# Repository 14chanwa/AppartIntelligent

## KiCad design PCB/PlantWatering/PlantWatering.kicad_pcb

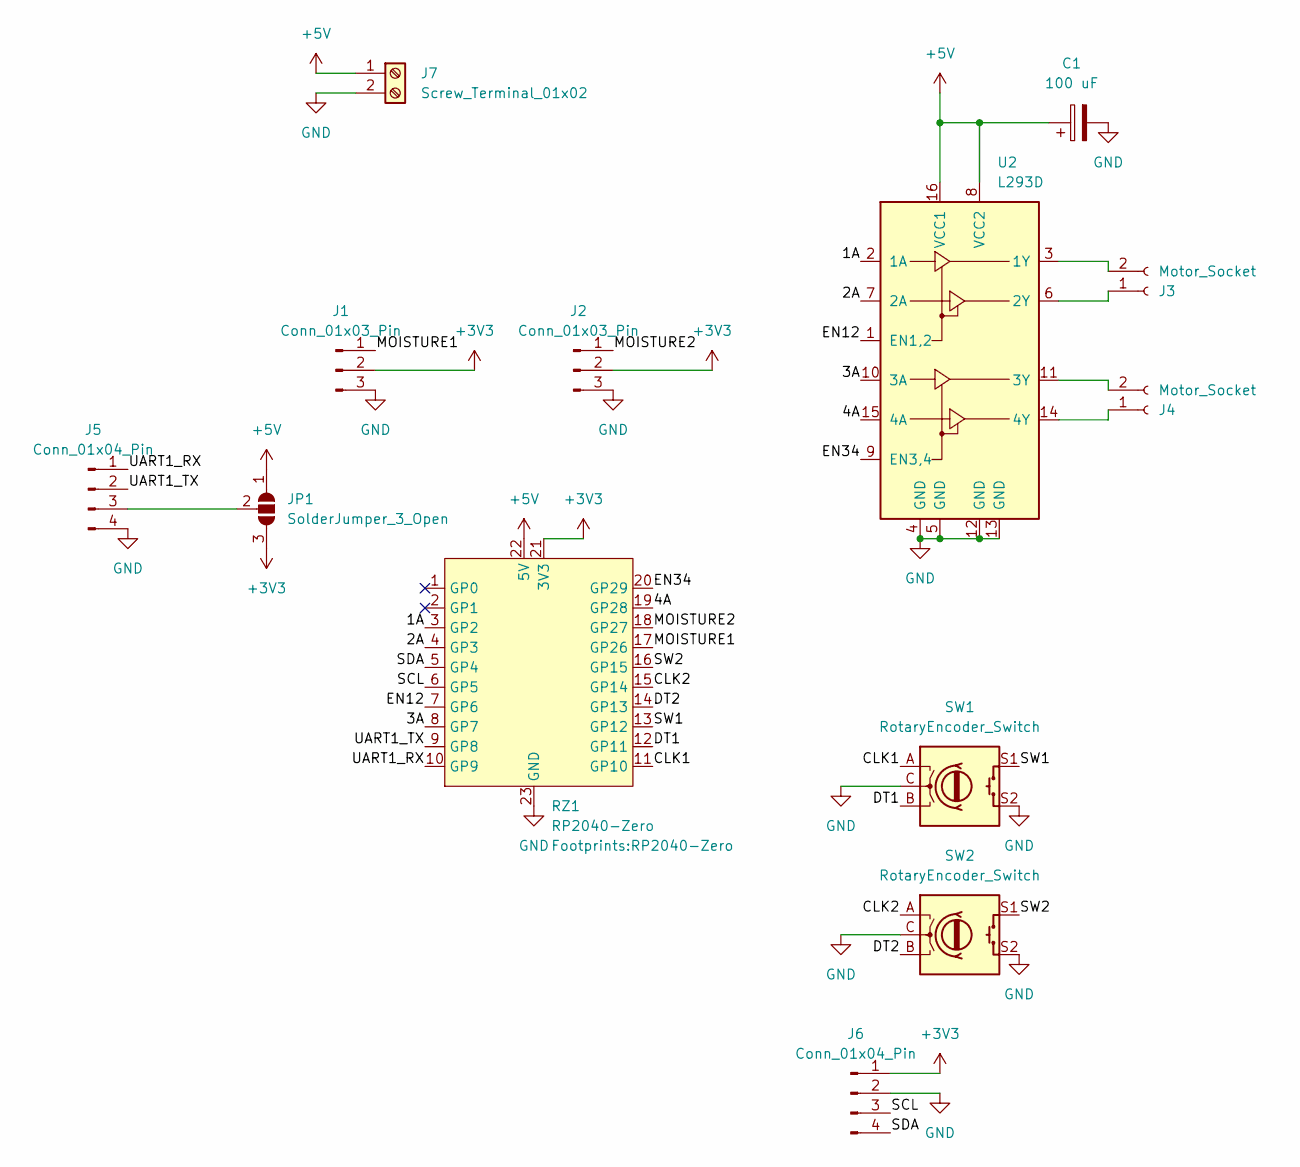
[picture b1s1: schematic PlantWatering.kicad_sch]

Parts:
C1: 100 uF; CP_Radial_D5.0mm_P2.50mm
J1, J2: Conn_01x03_Pin; PinHeader_1x03_P2.54mm_Vertical
J3, J4: Motor_Socket; PumpWatering
J5: Conn_01x04_Pin; PinHeader_1x04_P2.54mm_Vertical
J6: Conn_01x04_Pin; SSD1306
J7: Screw_Terminal_01x02; USBC-Dummy-Card
JP1: SolderJumper_3_Open; SolderJumper-3_P1.3mm_Open_RoundedPad1.0x1.5mm_NumberLabels
RZ1: RP2040-Zero
SW1, SW2: RotaryEncoder_Switch; RotaryEncoder_Alps_EC11E-Switch_Vertical_H20mm
U2: L293D; DIP-16_W7.62mm

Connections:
+3V3: J1.2, J2.2, J6.1, JP1.3 (B), RZ1.21 (3V3)
+5V: C1.1, J7.1, JP1.1 (A), RZ1.22 (5V), U2.8 (VCC2), U2.16 (VCC1)
/1A: RZ1.3 (GP2), U2.2 (1A)
/2A: RZ1.4 (GP3), U2.7 (2A)
/3A: RZ1.8 (GP7), U2.10 (3A)
/4A: RZ1.19 (GP28), U2.15 (4A)
/CLK1: RZ1.11 (GP10), SW1.A
/CLK2: RZ1.15 (GP14), SW2.A
/DT1: RZ1.12 (GP11), SW1.B
/DT2: RZ1.14 (GP13), SW2.B
/EN12: RZ1.7 (GP6), U2.1 (EN1,2)
/EN34: RZ1.20 (GP29), U2.9 (EN3,4)
/MOISTURE1: J1.1, RZ1.17 (GP26)
/MOISTURE2: J2.1, RZ1.18 (GP27)
/SCL: J6.3, RZ1.6 (GP5)
/SDA: J6.4, RZ1.5 (GP4)
/SW1: RZ1.13 (GP12), SW1.S1
/SW2: RZ1.16 (GP15), SW2.S1
/UART1_RX: J5.1, RZ1.10 (GP9)
/UART1_TX: J5.2, RZ1.9 (GP8)
GND: C1.2, J1.3, J2.3, J5.4, J6.2, J7.2, RZ1.23 (GND), SW1.C, SW1.S2, SW2.C, SW2.S2, U2.4 (GND), U2.5 (GND), U2.12 (GND), U2.13 (GND)
unnamed: J3.1, U2.6 (2Y)
unnamed: J3.2, U2.3 (1Y)
unnamed: J4.1, U2.14 (4Y)
unnamed: J4.2, U2.11 (3Y)
unnamed: J5.3, JP1.2 (C)

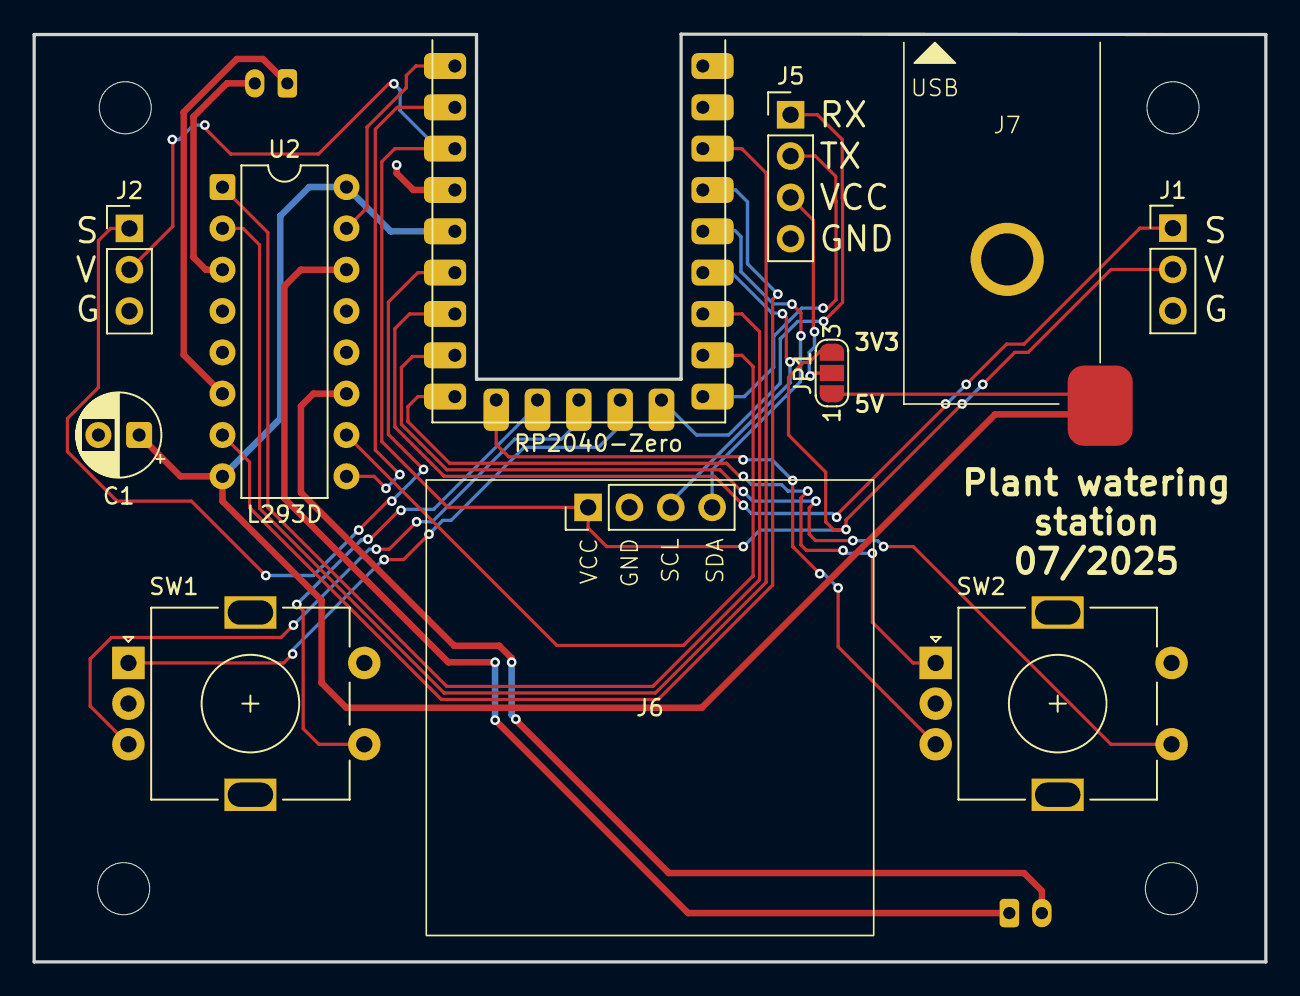
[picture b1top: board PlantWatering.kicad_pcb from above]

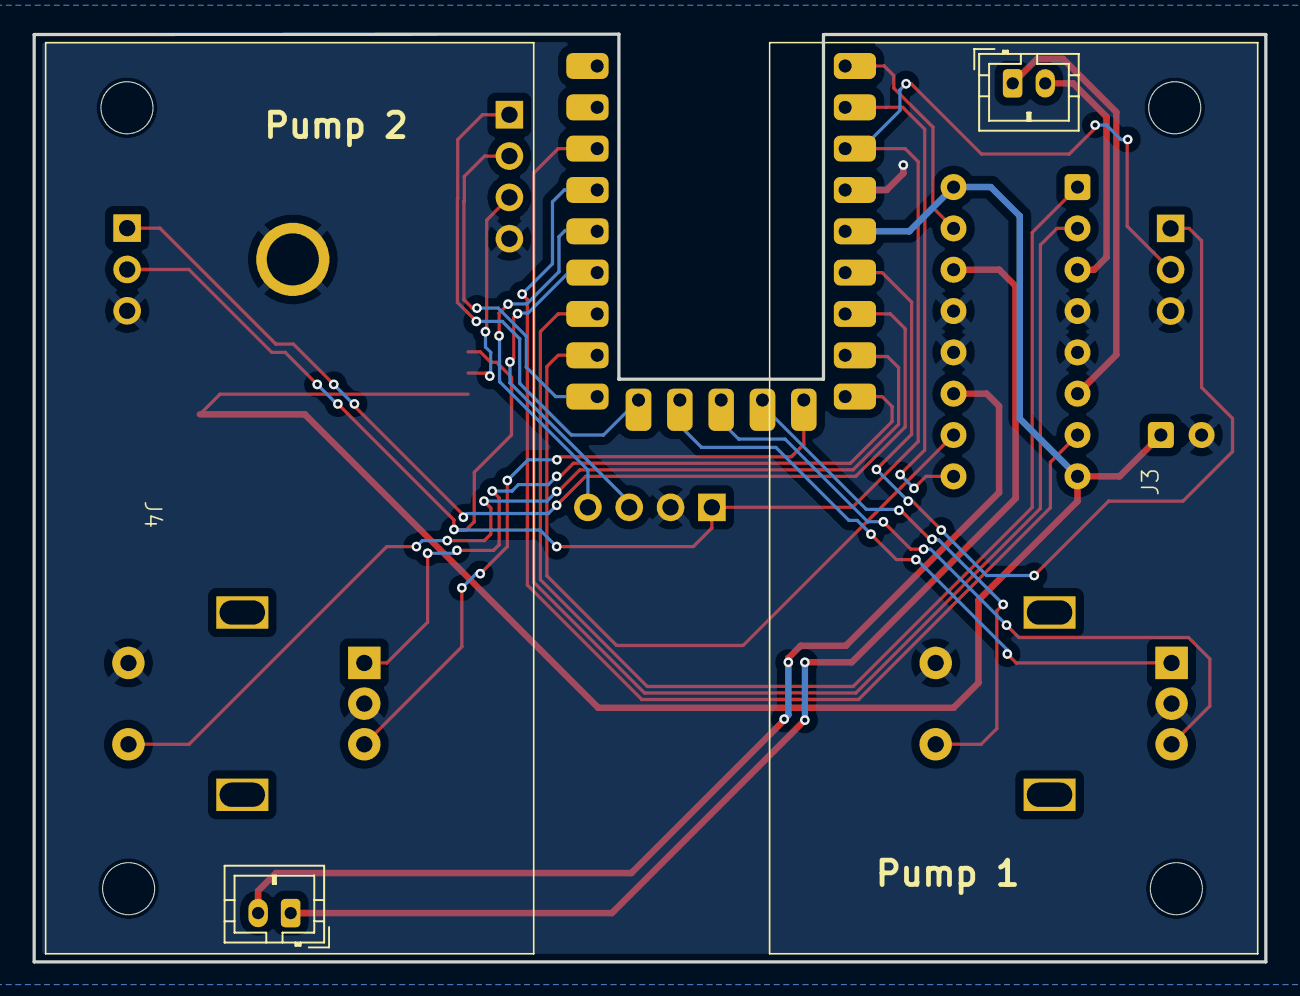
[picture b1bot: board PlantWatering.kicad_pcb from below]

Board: 2 copper layers, 75.7 x 57.0 mm, 13 parts (2 on the bottom side), 26 nets.

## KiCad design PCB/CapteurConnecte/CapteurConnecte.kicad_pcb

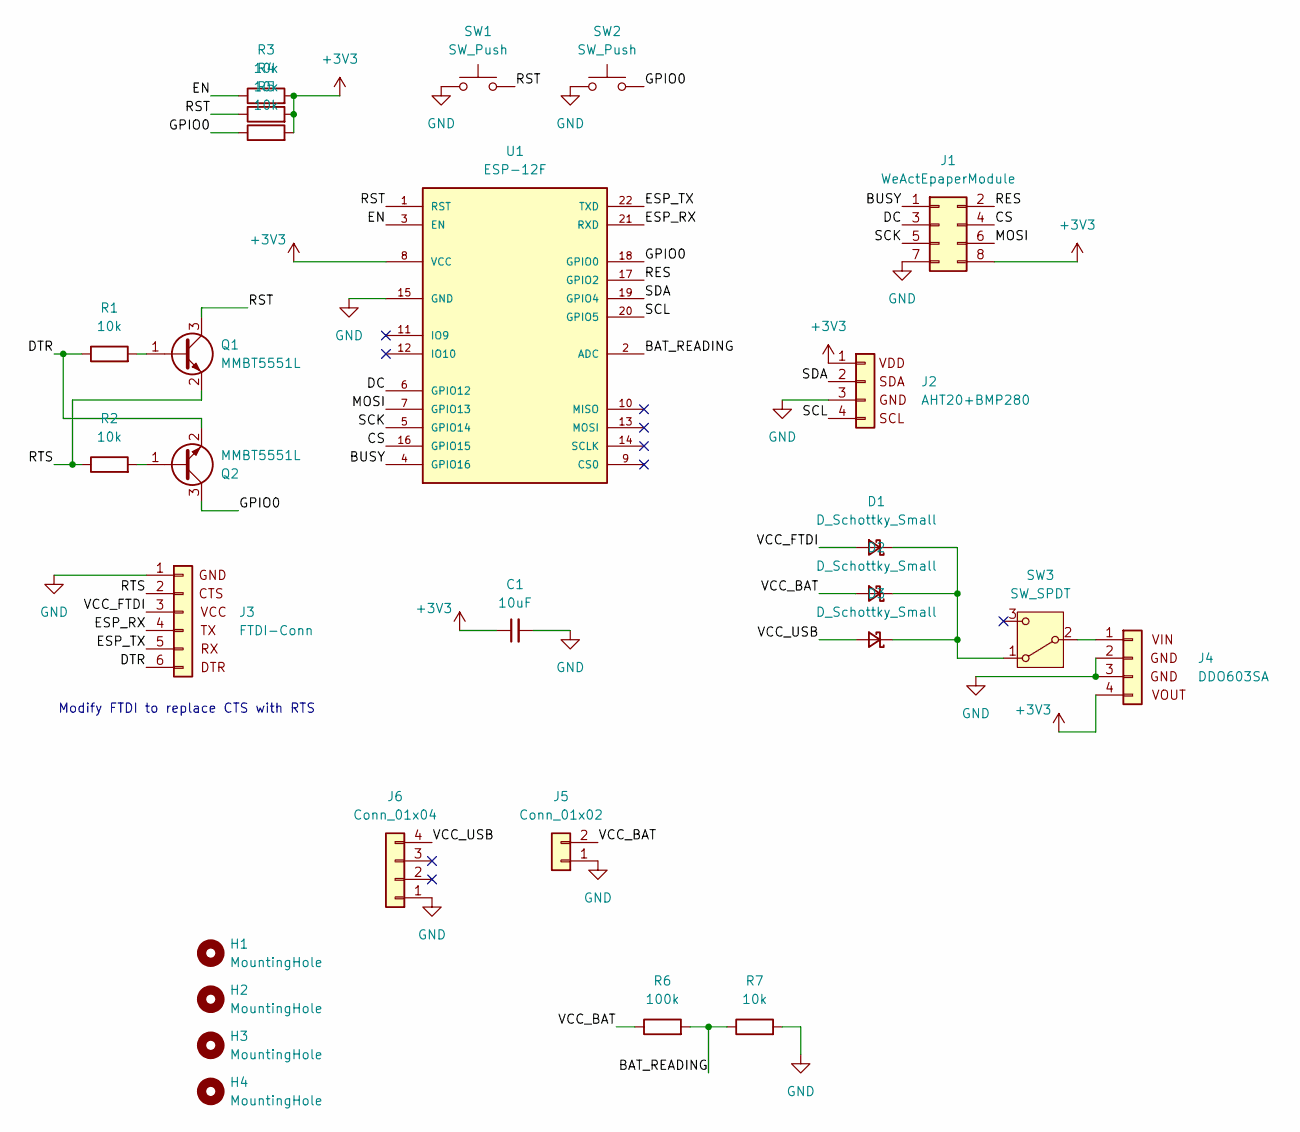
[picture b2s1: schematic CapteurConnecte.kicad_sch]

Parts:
C1: 10uF; CP_Radial_D4.0mm_P1.50mm
D1, D2, D3: D_Schottky_Small; D_SOD-323_HandSoldering
H1, H2, H3, H4: MountingHole; MountingHole_3.2mm_M3
J1: WeActEpaperModule; PinHeader_2x04_P2.54mm_Vertical
J2: AHT20+BMP280
J3: FTDI-Conn; FTDI-breakout
J4: DDO603SA; DD0603SB
J5: Conn_01x02; JST_PH_B2B-PH-K_1x02_P2.00mm_Vertical
J6: Conn_01x04; USBC-breakout
Q1, Q2: MMBT5551L; SOT-23
R1, R2, R3, R4, R5, R7: 10k; R_0805_2012Metric_Pad1.20x1.40mm_HandSolder
R6: 100k; R_0805_2012Metric_Pad1.20x1.40mm_HandSolder
SW1, SW2: SW_Push; SW_SPST_CK_RS282G05A3
SW3: SW_SPDT; SliderSwitch
U1: ESP-12F

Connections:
+3V3: C1.1, J1.8, J2.1, J4.4, R3.2, R4.2, R5.2, U1.8 (VCC)
/BAT_READING: R6.2, R7.1, U1.2 (ADC)
/BUSY: J1.1, U1.4 (GPIO16)
/CS: J1.4, U1.16 (GPIO15)
/DC: J1.3, U1.6 (GPIO12)
/DTR: J3.6, Q2.2 (E), R1.1
/EN: R3.1, U1.3 (EN)
/ESP_RX: J3.4, U1.21 (RXD)
/ESP_TX: J3.5, U1.22 (TXD)
/GPIO0: Q2.3 (C), R5.1, SW2.2, U1.18 (GPIO0)
/MOSI: J1.6, U1.7 (GPIO13)
/RES: J1.2, U1.17 (GPIO2)
/RST: Q1.3 (C), R4.1, SW1.2, U1.1 (RST)
/RTS: J3.2, Q1.2 (E), R2.1
/SCK: J1.5, U1.5 (GPIO14)
/SCL: J2.4, U1.20 (GPIO5)
/SDA: J2.2, U1.19 (GPIO4)
/VCC_BAT: D2.2 (A), J5.2, R6.1
/VCC_FTDI: D1.2 (A), J3.3
/VCC_USB: D3.2 (A), J6.4
GND: C1.2, J1.7, J2.3, J3.1, J4.2, J4.3, J5.1, J6.1, R7.2, SW1.1, SW2.1, U1.15 (GND)
unnamed: D1.1 (K), D2.1 (K), D3.1 (K), SW3.1 (A)
unnamed: J4.1, SW3.2 (B)
unnamed: Q1.1 (B), R1.2
unnamed: Q2.1 (B), R2.2

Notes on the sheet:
Modify FTDI to replace CTS with RTS

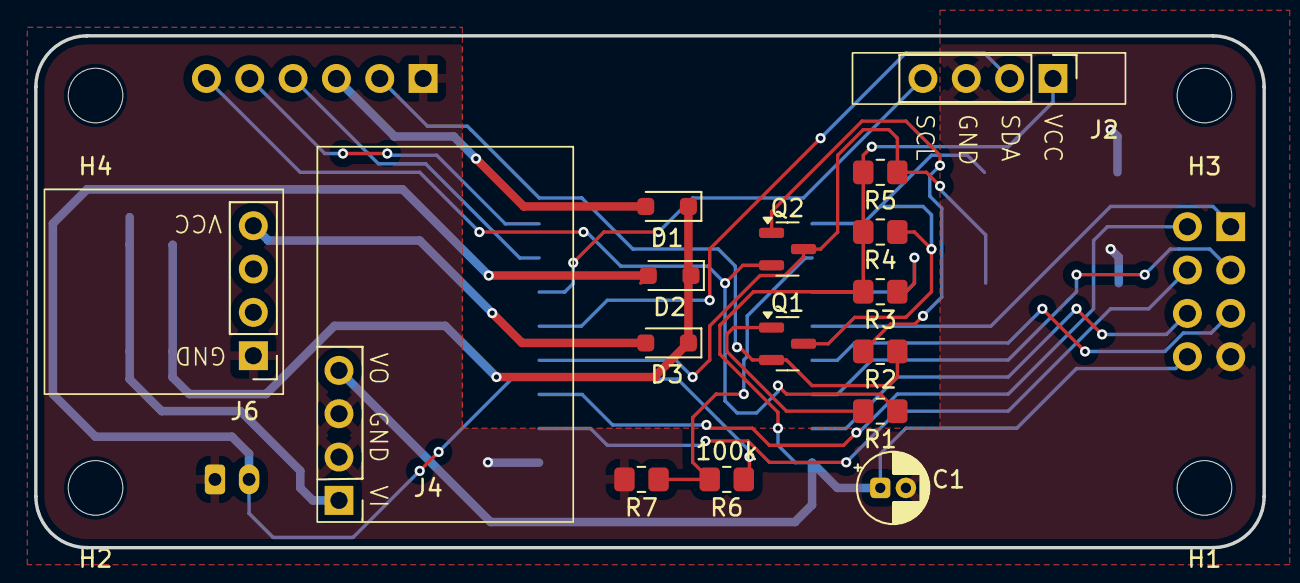
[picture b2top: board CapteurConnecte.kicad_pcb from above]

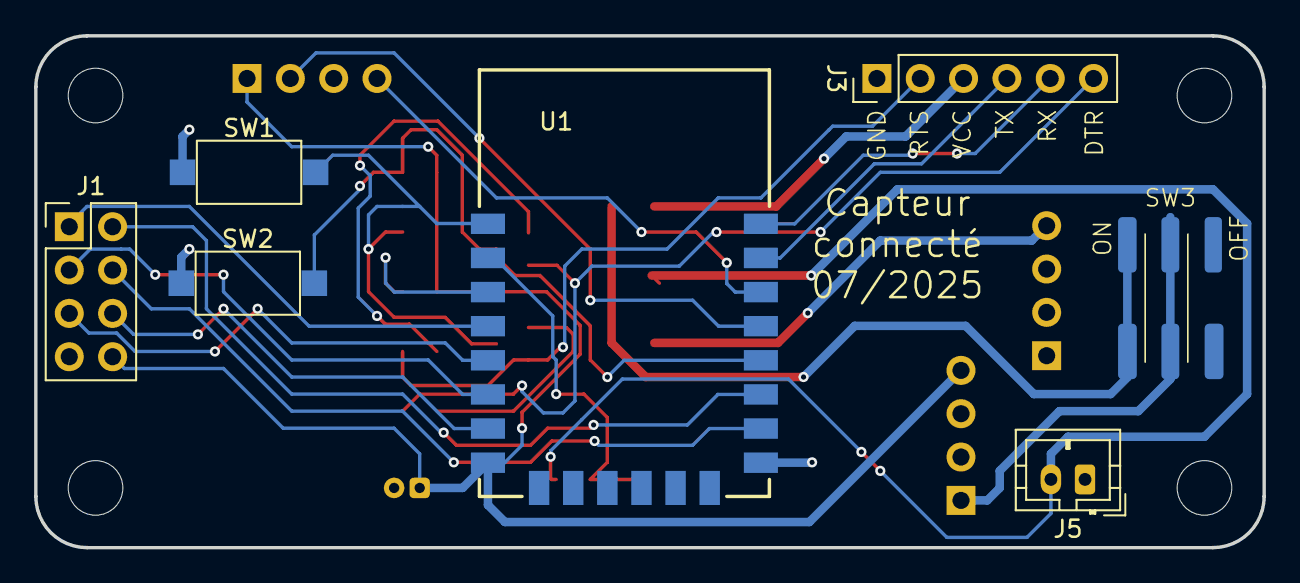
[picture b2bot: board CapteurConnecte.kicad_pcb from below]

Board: 2 copper layers, 72.0 x 30.0 mm, 27 parts (7 on the bottom side), 25 nets.

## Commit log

2025-07-27 Add initial capteur code
2025-08-14 Add plant watering code
